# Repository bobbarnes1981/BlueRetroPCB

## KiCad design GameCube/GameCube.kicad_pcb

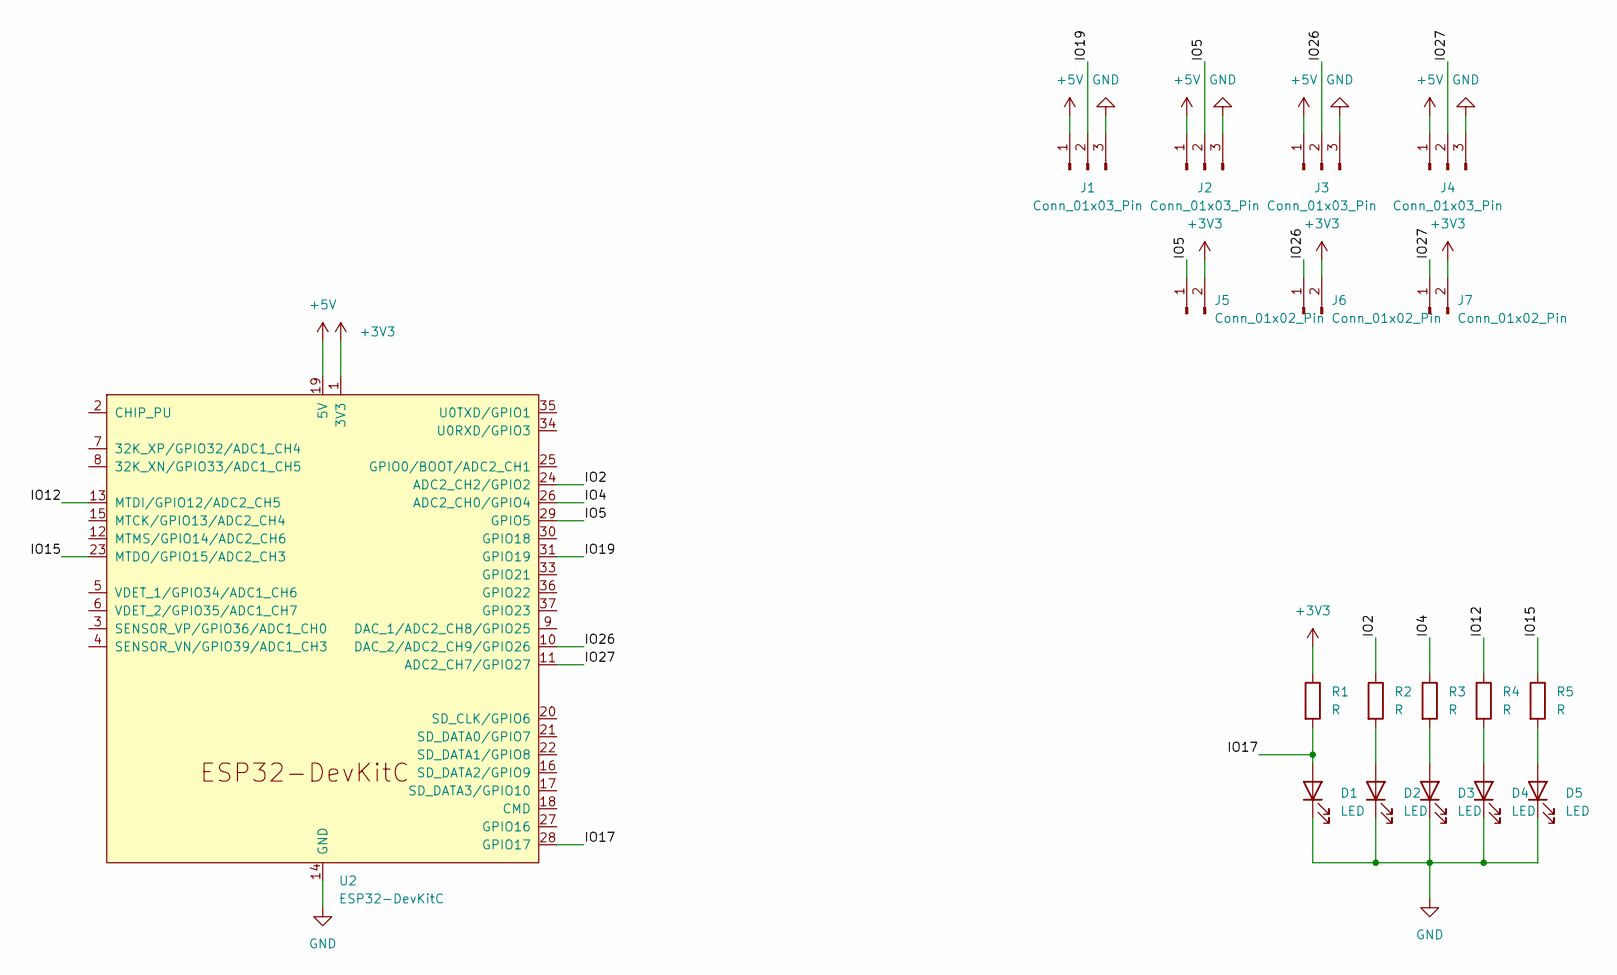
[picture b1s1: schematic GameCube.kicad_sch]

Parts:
D1, D2, D3, D4, D5: LED
J1, J2, J3, J4: Conn_01x03_Pin
J5, J6, J7: Conn_01x02_Pin
R1, R2, R3, R4, R5: R
U2: ESP32-DevKitC

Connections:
+3V3: J5.2, J6.2, J7.2, R1.1, U2.1 (3V3)
+5V: J1.1, J2.1, J3.1, J4.1, U2.19 (5V)
/IO2: R2.1, U2.24 (ADC2_CH2/GPIO2)
/IO4: R3.1, U2.26 (ADC2_CH0/GPIO4)
/IO5: J2.2, J5.1, U2.29 (GPIO5)
/IO12: R4.1, U2.13 (MTDI/GPIO12/ADC2_CH5)
/IO15: R5.1, U2.23 (MTDO/GPIO15/ADC2_CH3)
/IO17: D1.2 (A), R1.2, U2.28 (GPIO17)
/IO19: J1.2, U2.31 (GPIO19)
/IO26: J3.2, J6.1, U2.10 (DAC_2/ADC2_CH9/GPIO26)
/IO27: J4.2, J7.1, U2.11 (ADC2_CH7/GPIO27)
GND: D1.1 (K), D2.1 (K), D3.1 (K), D4.1 (K), D5.1 (K), J1.3, J2.3, J3.3, J4.3, U2.14 (GND), U2.32 (GND), U2.38 (GND)
unnamed: D2.2 (A), R2.2
unnamed: D3.2 (A), R3.2
unnamed: D4.2 (A), R4.2
unnamed: D5.2 (A), R5.2

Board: 2 copper layers, 18 parts (0 on the bottom side), 16 nets, no tracks yet.

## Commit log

2025-01-22 Move esp32
2025-01-22 Add esp32 footprints and pcb outline
2025-01-24 Add footprints and rough layout
